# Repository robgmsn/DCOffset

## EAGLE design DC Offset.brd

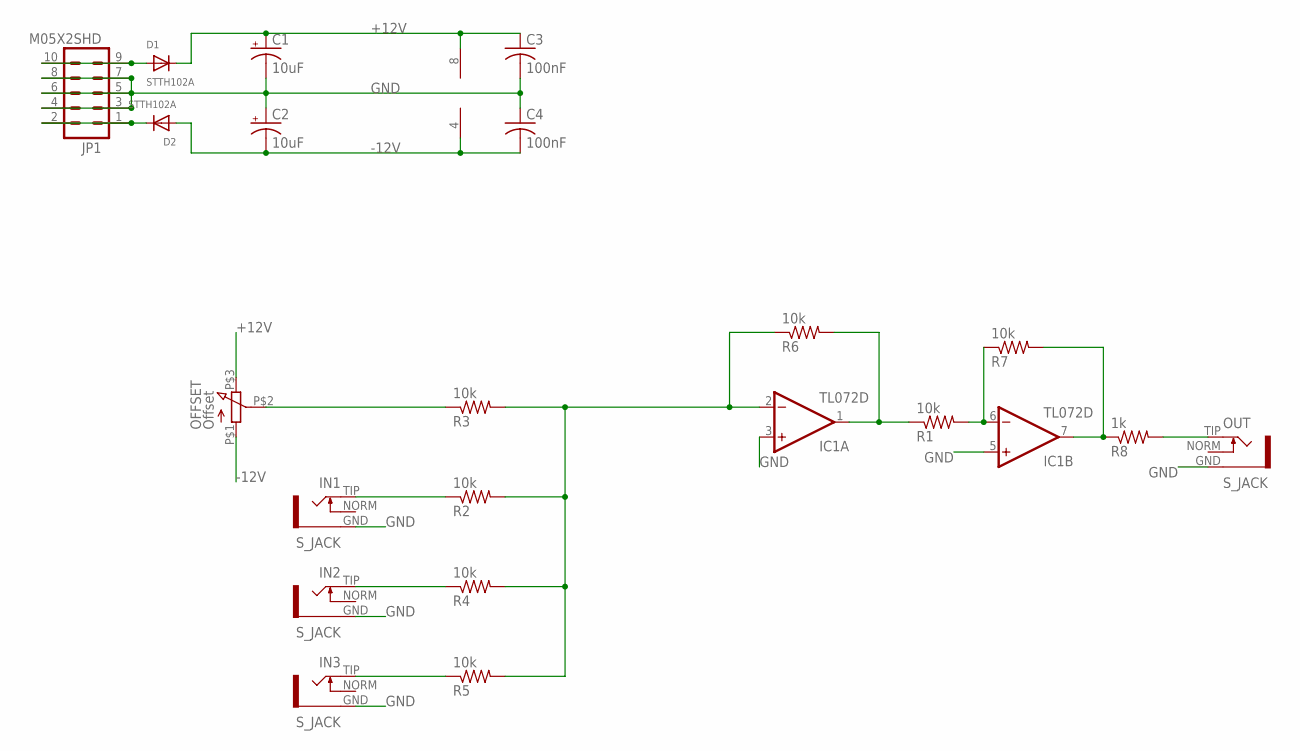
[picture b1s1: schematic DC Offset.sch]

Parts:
C1, C2: 10uF; 153CLV-0505
C3, C4: 100nF; C0805
D1, D2: STTH102A; SMADIODE
IC1: TL072D; SO08
IN1, IN2, IN3: S_JACK
JP1: M05X2SHD; 2X5-SHROUDED
OFFSET: Offset; Q-POT
OUT: S_JACK
R1, R2, R3, R4, R5, R6, R7: 10k; R0805
R8: 1k; R0805

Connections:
+12V: C1.+, C3.1, D1.C, IC1.8 (V+), OFFSET.P$3 (3)
-12V: C2.-, C4.2, D2.A, IC1.4 (V-), OFFSET.P$1 (1)
GND: C1.-, C2.+, C3.2, C4.1, IC1.3 (+IN), IC1.5 (+IN), IN1.GND, IN2.GND, IN3.GND, JP1.3, JP1.4, JP1.5, JP1.6, JP1.7, JP1.8, OUT.GND
unnamed: D1.A, JP1.9, JP1.10
unnamed: IC1.7 (OUT), R7.2, R8.1
unnamed: OUT.TIP, R8.2
unnamed: IC1.6 (-IN), R1.2, R7.1
unnamed: OFFSET.P$2 (2), R3.1
unnamed: IC1.2 (-IN), R2.2, R3.2, R4.2, R5.2, R6.1
unnamed: D2.C, JP1.1, JP1.2
unnamed: IC1.1 (OUT), R1.1, R6.2
unnamed: IN1.TIP, R2.1
unnamed: IN2.TIP, R4.1
unnamed: IN3.TIP, R5.1

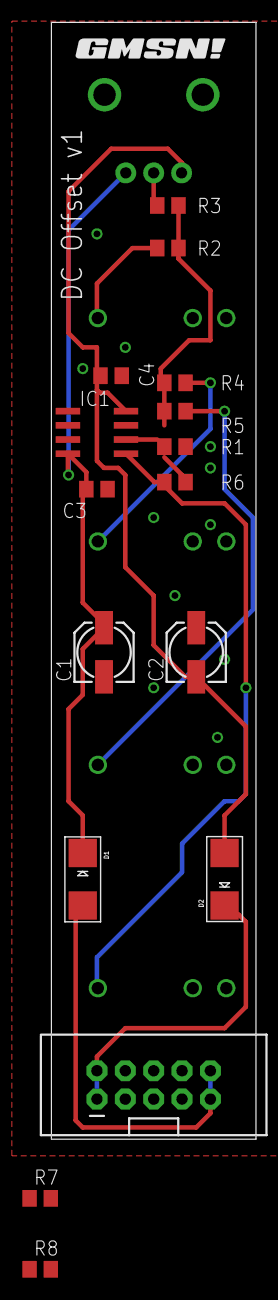
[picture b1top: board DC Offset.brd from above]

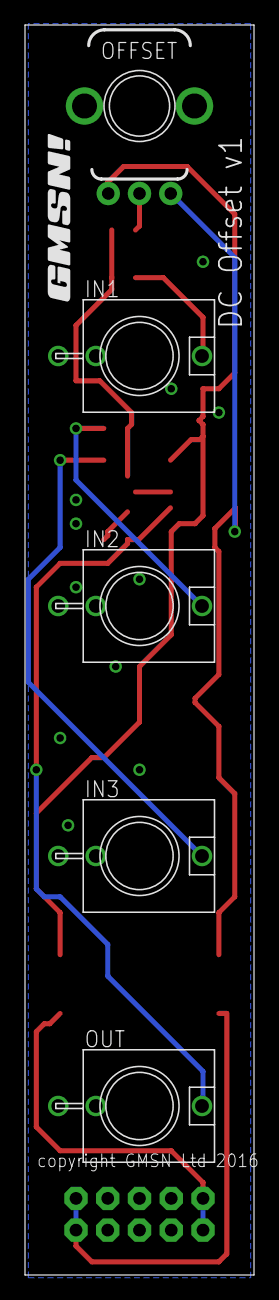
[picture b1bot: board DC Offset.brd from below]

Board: 2 copper layers, 18.3 x 100.0 mm, 23 parts (6 on the bottom side), 14 nets.

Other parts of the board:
U$1, U$2: GMSN!_LOGO

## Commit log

2021-04-25 DC Offset 1.0
    Moved to it's own repo
2021-07-07 Reinstall

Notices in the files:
DC Offset.brd:
copyright GMSN Ltd 2016
